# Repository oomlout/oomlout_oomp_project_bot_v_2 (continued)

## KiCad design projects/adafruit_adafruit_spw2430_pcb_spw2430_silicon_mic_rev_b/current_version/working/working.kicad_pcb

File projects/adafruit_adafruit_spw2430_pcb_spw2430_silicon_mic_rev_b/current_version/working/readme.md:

# adafruit_spw2430_pcb
 
## summary 
* id: adafruit_adafruit_spw2430_pcb_spw2430_silicon_mic_rev_b
* user: adafruit
* name: adafruit_spw2430_pcb
* board: spw2430_silicon_mic_rev_b
* repo: https://github.com/adafruit/Adafruit-SPW2430-PCB

* src_file_repo_sch: 
* src_file_repo_sch_link: https://github.com/adafruit/Adafruit-SPW2430-PCB/tree/master/
* full details link: https://github.com/oomlout/oomlout_oomp_project_bot_v_2/tree/main/projects/adafruit_adafruit_spw2430_pcb_spw2430_silicon_mic_rev_b/current_version/working  

## schematic  
  
[schematic (pdf)](working_schematic.pdf) 

## pcb  

[board (pdf)](working.pdf)  

## working_bom
| Id | Designator | Footprint | Quantity | Designation | Supplier and ref |  | None | 
| --- | --- | --- | --- | --- | --- | --- | --- | 
| 1 | C2 | 0805-NO | 1 | 0.1uF |  |  | [''] | 
| 2 | JP1 | 1X05_ROUND_76 | 1 |  |  |  | [''] | 
| 3 | U1 | SPW2430HR5H-B | 1 | SPW2430HR5H-B |  |  | [''] | 
| 4 | U2 | SOT23-5 | 1 | MIC5225-3.3 |  |  | [''] | 
| 5 | C3,C1,C4 | 0805-NO | 3 | 10uF |  |  | [''] | 
| 6 | U$12 | MOUNTINGHOLE_2.5_PLATED | 1 | MOUNTINGHOLE2.5 |  |  | [''] | 
| 7 | U$13 | PCBFEAT-REV-040 | 1 |  |  |  | [''] | 
| 8 | FID1,FID2 | FIDUCIAL_1MM | 2 | FIDUCIAL" |  |  | [''] | 
| 9 | U$5 | ADAFRUIT_3.5MM | 1 |  |  |  | [''] | 

## bom_schematic
| Ref | Qnty | Value | Cmp name | Footprint | Description | Vendor | DNP | 
| --- | --- | --- | --- | --- | --- | --- | --- | 
| C1, C3, C4 | 3 | 10uF | CAP_CERAMIC0805-NOOUTLINE | working:0805-NO |  |  |  | 
| C2 | 1 | 0.1uF | CAP_CERAMIC0805-NOOUTLINE | working:0805-NO |  |  |  | 
| FID1, FID2 | 2 | FIDUCIAL"" | FIDUCIAL{dblquote}{dblquote} | working:FIDUCIAL_1MM |  |  |  | 
| JP1 | 1 | HEADER-1X576MIL | HEADER-1X576MIL | working:1X05_ROUND_76 |  |  |  | 
| U1 | 1 | SPW2430HR5H-B | SPW2430HR5H-B | working:SPW2430HR5H-B |  |  |  | 
| U2 | 1 | MIC5225-3.3 | VREG_SOT23-5 | working:SOT23-5 |  |  |  | 
| U$12 | 1 | MOUNTINGHOLE2.5 | MOUNTINGHOLE2.5 | working:MOUNTINGHOLE_2.5_PLATED |  |  |  | 

## mounting_holes
| x | y | package | value | ref | size | 
| --- | --- | --- | --- | --- | --- | 
| 0.0 | 0.0 | MOUNTINGHOLE_2.5_PLATED | MOUNTINGHOLE2.5 | U$12 | m3 |

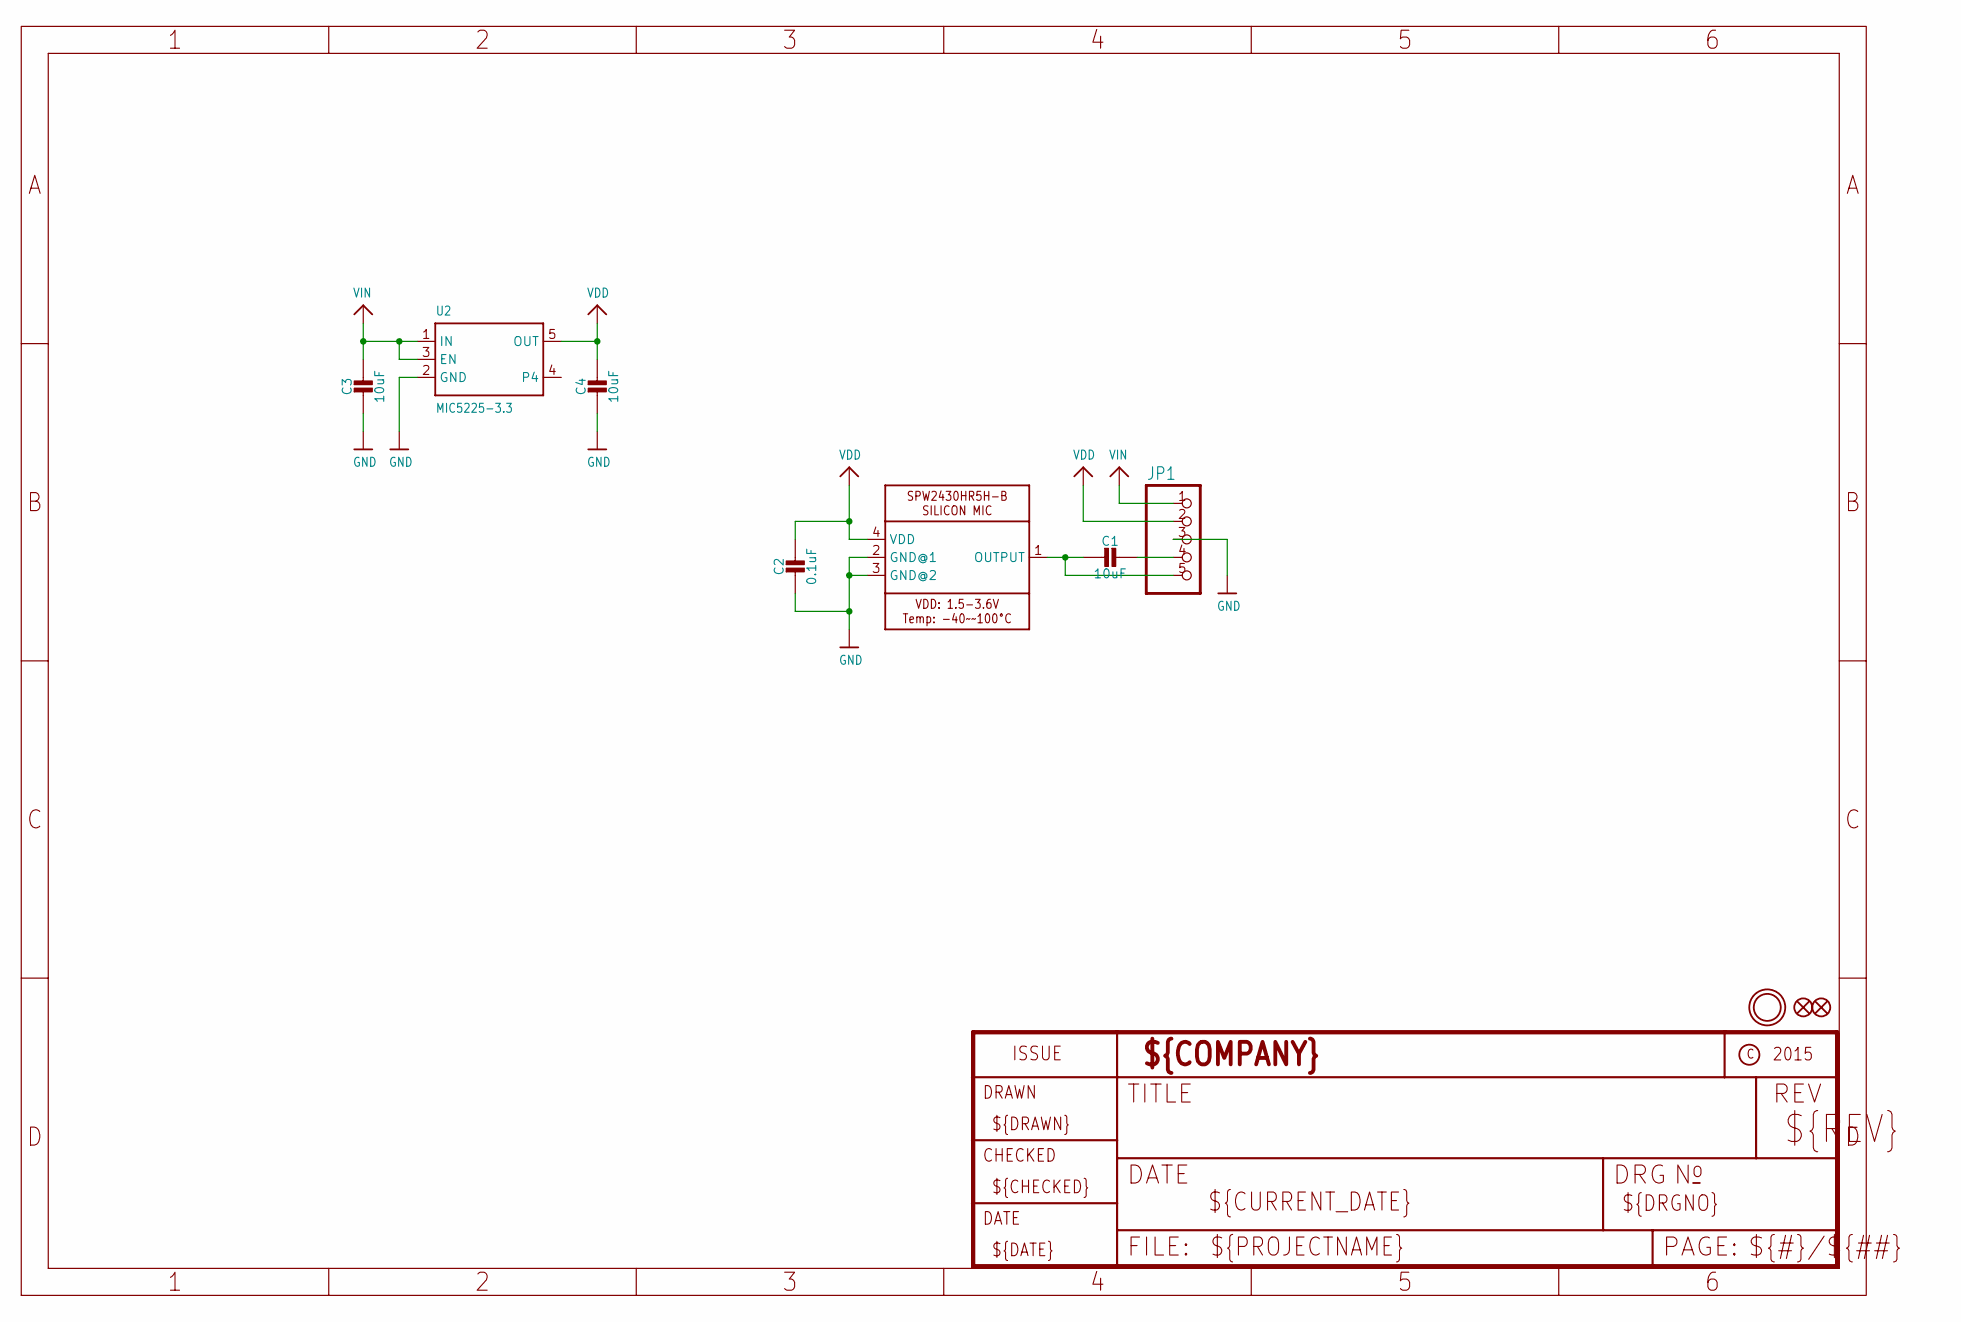
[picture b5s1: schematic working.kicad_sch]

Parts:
C1, C3, C4: 10uF; 0805-NO
C2: 0.1uF; 0805-NO
FID1, FID2: FIDUCIAL""; FIDUCIAL_1MM
JP1: HEADER-1X576MIL; 1X05_ROUND_76
U1: SPW2430HR5H-B
U2: MIC5225-3.3; SOT23-5
U$12: MOUNTINGHOLE2.5; MOUNTINGHOLE_2.5_PLATED

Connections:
GND: C2.2, C3.2, C4.2, JP1.3, U1.2 (GND@1), U1.3 (GND@2), U2.2 (GND)
unnamed: C1.2, JP1.5, U1.1 (OUTPUT)
unnamed: C1.1, JP1.4
VDD: C2.1, C4.1, JP1.2, U1.4 (VDD), U2.5 (OUT)
VIN: C3.1, JP1.1, U2.1 (IN), U2.3 (EN)

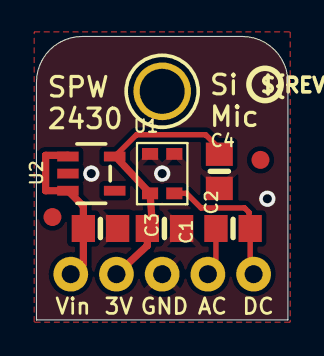
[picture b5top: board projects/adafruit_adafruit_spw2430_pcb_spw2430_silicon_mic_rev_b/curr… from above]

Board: 2 copper layers, 14.0 x 15.7 mm, 12 parts (1 on the bottom side), 5 nets.

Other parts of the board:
U$5: ADAFRUIT_3.5MM
U$13: PCBFEAT-REV-040

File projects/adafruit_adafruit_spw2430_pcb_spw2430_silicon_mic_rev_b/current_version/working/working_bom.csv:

"Id";"Designator";"Footprint";"Quantity";"Designation";"Supplier and ref";
1;"C2";"0805-NO";1;"0.1uF";;;
2;"JP1";"1X05_ROUND_76";1;"";;;
3;"U1";"SPW2430HR5H-B";1;"SPW2430HR5H-B";;;
4;"U2";"SOT23-5";1;"MIC5225-3.3";;;
5;"C3,C1,C4";"0805-NO";3;"10uF";;;
6;"U$12";"MOUNTINGHOLE_2.5_PLATED";1;"MOUNTINGHOLE2.5";;;
7;"U$13";"PCBFEAT-REV-040";1;"";;;
8;"FID1,FID2";"FIDUCIAL_1MM";2;"FIDUCIAL""";;;
9;"U$5";"ADAFRUIT_3.5MM";1;"";;;

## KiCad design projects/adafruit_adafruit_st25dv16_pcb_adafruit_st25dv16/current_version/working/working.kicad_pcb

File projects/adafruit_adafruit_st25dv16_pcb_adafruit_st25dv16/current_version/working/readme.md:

# adafruit_st25dv16_pcb
 
## summary 
* id: adafruit_adafruit_st25dv16_pcb_adafruit_st25dv16
* user: adafruit
* name: adafruit_st25dv16_pcb
* board: adafruit_st25dv16
* repo: https://github.com/adafruit/Adafruit-ST25DV16-PCB

* src_file_repo_sch: 
* src_file_repo_sch_link: https://github.com/adafruit/Adafruit-ST25DV16-PCB/tree/main/
* full details link: https://github.com/oomlout/oomlout_oomp_project_bot_v_2/tree/main/projects/adafruit_adafruit_st25dv16_pcb_adafruit_st25dv16/current_version/working  

## schematic  
  
[schematic (pdf)](working_schematic.pdf) 

## pcb  

[board (pdf)](working.pdf)  

## working_bom
| Id | Designator | Footprint | Quantity | Designation | Supplier and ref |  | None | 
| --- | --- | --- | --- | --- | --- | --- | --- | 
| 1 | @HOLE0,@HOLE1 |  | 2 |  |  |  | [''] | 
| 2 | CONN3,CONN4 | JST_SH4 | 2 | STEMMA_I2C_QT |  |  | [''] | 
| 3 | U$19,U$21 | MOUNTINGHOLE_2.5_PLATED | 2 | MOUNTINGHOLE2.5 |  |  | [''] | 
| 4 | FID3,FID4 | FIDUCIAL_1MM | 2 | FIDUCIAL_1MM |  |  | [''] | 
| 5 | D1 | CHIPLED_0603_NOOUTLINE | 1 | GREEN |  |  | [''] | 
| 6 | C1 | 0603-NO | 1 | 0.1uF |  |  | [''] | 
| 7 | R3 | RESPACK_4X0603 | 1 | 10K |  |  | [''] | 
| 8 | C3 | 0805-NO | 1 | 10uF |  |  | [''] | 
| 9 | ANT1 | NFCANT_25X15 | 1 | NFC_ANTENNA_25X15 |  |  | [''] | 
| 10 | JP1 | 1X06_ROUND_70 | 1 |  |  |  | [''] | 
| 11 | U$22 | ADAFRUIT_3.5MM | 1 |  |  |  | [''] | 
| 12 | RF1 | TSSOP8-4.4MM | 1 | ST25DVXX_TSSOP |  |  | [''] | 
| 13 | U$1 | ADAFRUIT_TEXT_20MM | 1 |  |  |  | [''] | 
| 14 | U$31,U$30 | STEMMAQT | 2 |  |  |  | [''] | 
| 15 | U$25 | PCBFEAT-REV-040 | 1 |  |  |  | [''] | 

## bom_schematic
| Ref | Qnty | Value | Cmp name | Footprint | Description | Vendor | DNP | 
| --- | --- | --- | --- | --- | --- | --- | --- | 
| ANT1 | 1 | NFC_ANTENNA_25X15 | NFC_ANTENNA_25X15 | working:NFCANT_25X15 |  |  |  | 
| C1 | 1 | 0.1uF | CAP_CERAMIC0603_NO | working:0603-NO |  |  |  | 
| C3 | 1 | 10uF | CAP_CERAMIC0805-NOOUTLINE | working:0805-NO |  |  |  | 
| CONN3, CONN4 | 2 | STEMMA_I2C_QT | STEMMA_I2C_QT | working:JST_SH4 |  |  |  | 
| D1 | 1 | GREEN | LED0603_NOOUTLINE | working:CHIPLED_0603_NOOUTLINE |  |  |  | 
| FID3, FID4 | 2 | FIDUCIAL_1MM | FIDUCIAL_1MM | working:FIDUCIAL_1MM |  |  |  | 
| JP1 | 1 | HEADER-1X670MIL | HEADER-1X670MIL | working:1X06_ROUND_70 |  |  |  | 
| R3 | 1 | 10K | RESISTOR_4PACK | working:RESPACK_4X0603 |  |  |  | 
| RF1 | 1 | ST25DVXX_TSSOP | ST25DVXX_TSSOP | working:TSSOP8-4.4MM |  |  |  | 
| U$19, U$21 | 2 | MOUNTINGHOLE2.5 | MOUNTINGHOLE2.5 | working:MOUNTINGHOLE_2.5_PLATED |  |  |  | 

## mounting_holes
| x | y | package | value | ref | size | 
| --- | --- | --- | --- | --- | --- | 
| 0.0 | 0.0 | MOUNTINGHOLE_2.5_PLATED | MOUNTINGHOLE2.5 | U$19 | m3 | 
| 20.32 | 0.0 | MOUNTINGHOLE_2.5_PLATED | MOUNTINGHOLE2.5 | U$21 | m3 |

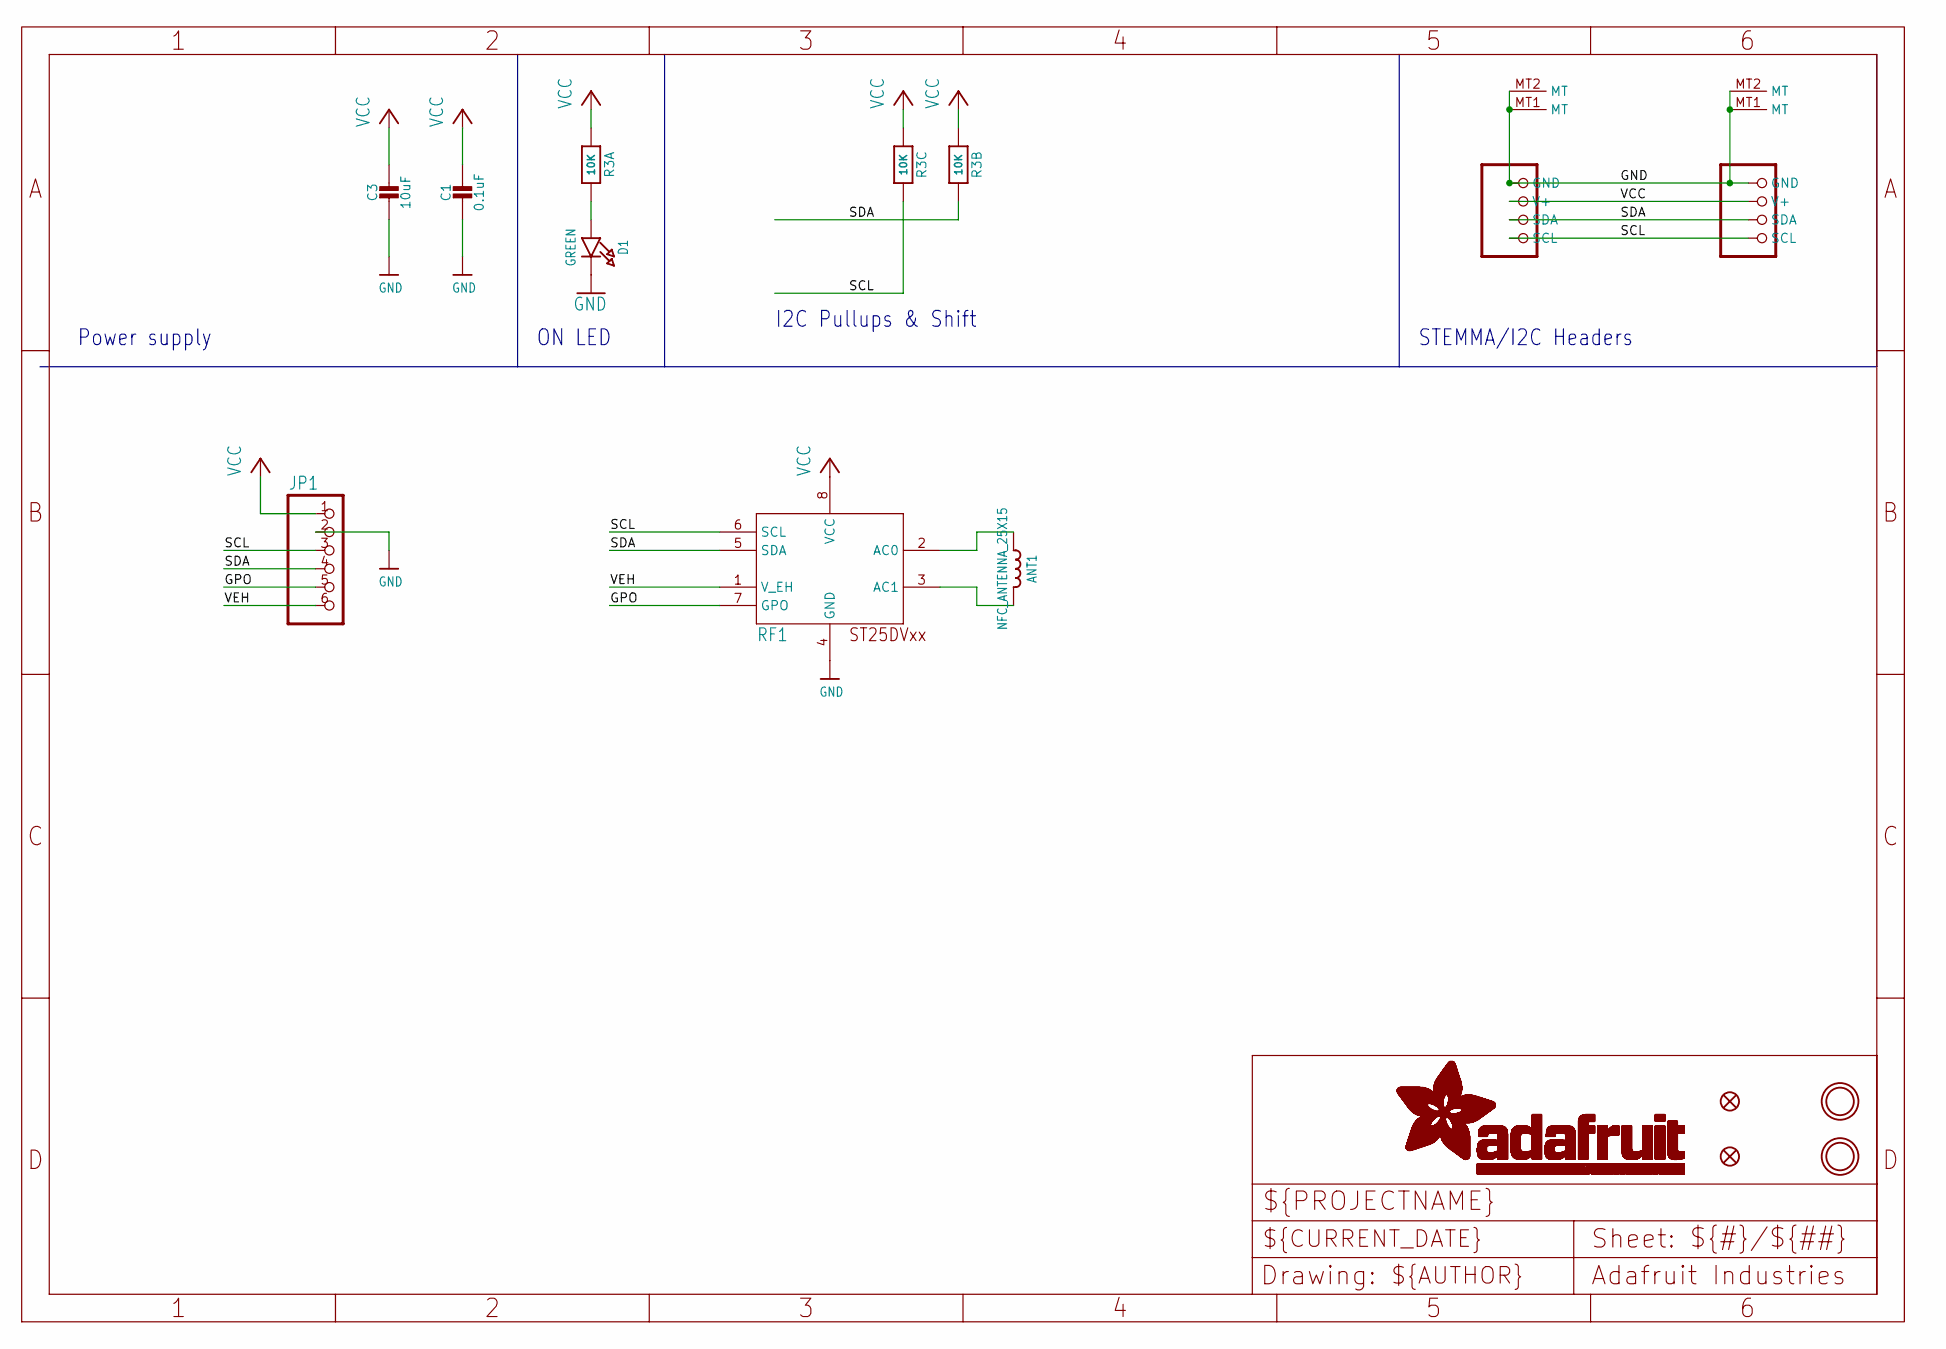
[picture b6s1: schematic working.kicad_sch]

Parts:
ANT1: NFC_ANTENNA_25X15; NFCANT_25X15
C1: 0.1uF; 0603-NO
C3: 10uF; 0805-NO
CONN3, CONN4: STEMMA_I2C_QT; JST_SH4
D1: GREEN; CHIPLED_0603_NOOUTLINE
FID3, FID4: FIDUCIAL_1MM
JP1: HEADER-1X670MIL; 1X06_ROUND_70
R3: 10K; RESPACK_4X0603
RF1: ST25DVXX_TSSOP; TSSOP8-4.4MM
U$19, U$21: MOUNTINGHOLE2.5; MOUNTINGHOLE_2.5_PLATED

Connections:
GND: C1.2, C3.2, CONN3.1 (GND), CONN3.MT1 (MT), CONN3.MT2 (MT), CONN4.1 (GND), CONN4.MT1 (MT), CONN4.MT2 (MT), D1.C, JP1.2, RF1.4 (GND)
GPO: JP1.5, RF1.7 (GPO)
unnamed: D1.A, R3.8 (2)
unnamed: ANT1.P$2 (2), RF1.2 (AC0)
unnamed: ANT1.P$1 (1), RF1.3 (AC1)
SCL: CONN3.4 (SCL), CONN4.4 (SCL), JP1.3, R3.6 (2), RF1.6 (SCL)
SDA: CONN3.3 (SDA), CONN4.3 (SDA), JP1.4, R3.7 (2), RF1.5 (SDA)
VCC: C1.1, C3.1, CONN3.2 (V+), CONN4.2 (V+), JP1.1, R3.1, R3.2 (1), R3.3 (1), RF1.8 (VCC)
VEH: JP1.6, RF1.1 (V_EH)

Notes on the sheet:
ON LED
I2C Pullups & Shift
STEMMA/I2C Headers
Power supply

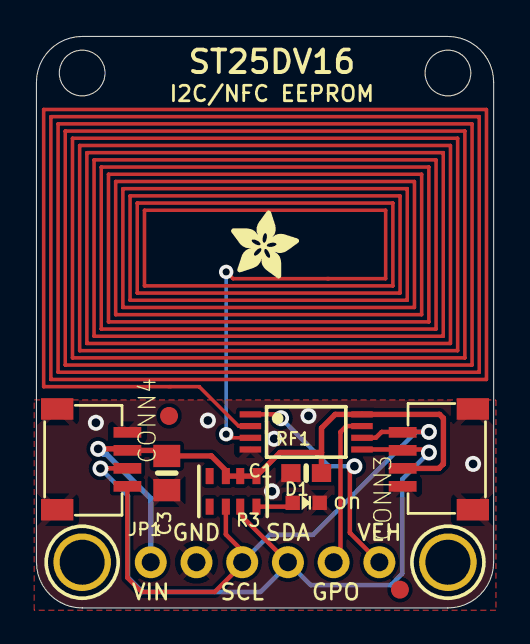
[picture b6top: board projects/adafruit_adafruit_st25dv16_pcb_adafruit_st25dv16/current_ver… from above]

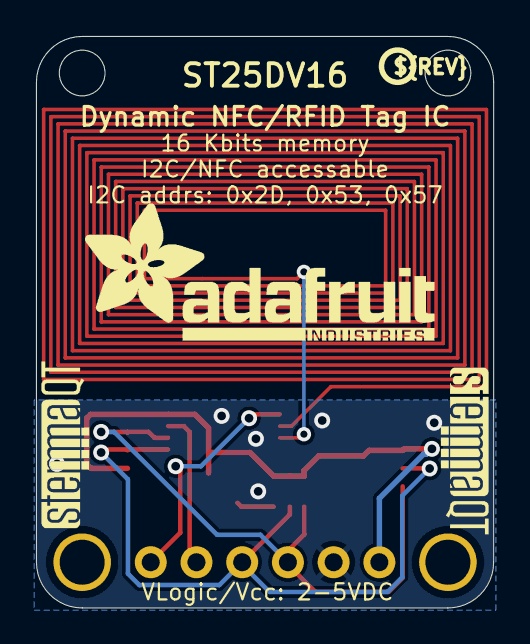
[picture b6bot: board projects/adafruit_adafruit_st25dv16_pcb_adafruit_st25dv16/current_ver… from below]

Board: 2 copper layers, 25.4 x 31.8 mm, 20 parts (4 on the bottom side), 9 nets.

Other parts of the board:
@HOLE0, @HOLE1: (no value)
U$1: ADAFRUIT_TEXT_20MM
U$22: ADAFRUIT_3.5MM
U$25: PCBFEAT-REV-040
U$30, U$31: STEMMAQT

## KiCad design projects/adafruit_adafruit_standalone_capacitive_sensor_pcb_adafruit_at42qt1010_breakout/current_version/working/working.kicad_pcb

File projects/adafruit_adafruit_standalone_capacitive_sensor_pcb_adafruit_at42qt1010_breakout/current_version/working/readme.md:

# adafruit_standalone_capacitive_sensor_pcb
 
## summary 
* id: adafruit_adafruit_standalone_capacitive_sensor_pcb_adafruit_at42qt1010_breakout
* user: adafruit
* name: adafruit_standalone_capacitive_sensor_pcb
* board: adafruit_at42qt1010_breakout
* repo: https://github.com/adafruit/Adafruit-Standalone-Capacitive-Sensor-PCB

* src_file_repo_sch: 
* src_file_repo_sch_link: https://github.com/adafruit/Adafruit-Standalone-Capacitive-Sensor-PCB/tree/master/
* full details link: https://github.com/oomlout/oomlout_oomp_project_bot_v_2/tree/main/projects/adafruit_adafruit_standalone_capacitive_sensor_pcb_adafruit_at42qt1010_breakout/current_version/working  

## schematic  
  
[schematic (pdf)](working_schematic.pdf) 

## pcb  

[board (pdf)](working.pdf)  

## working_bom
| Id | Designator | Footprint | Quantity | Designation | Supplier and ref |  | None | 
| --- | --- | --- | --- | --- | --- | --- | --- | 
| 1 | SJ1 | SOLDERJUMPER_CLOSEDWIRE | 1 | LED |  |  | [''] | 
| 2 | U$9,U$6,U$10,U$11 | MOUNTINGHOLE_2.5_PLATED | 4 | MOUNTINGHOLE2.5 |  |  | [''] | 
| 3 | SJ2 | SOLDERJUMPER_2WAY_OPEN_NOPASTE | 1 | MODE |  |  | [''] | 
| 4 | JP1 | 1X04_ROUND_76 | 1 |  |  |  | [''] | 
| 5 | LED1 | PLCC2_REVMOUNT | 1 | LS T77K-J1L2-1-0-2-R18-Z |  |  | [''] | 
| 6 | R1 | _0805 | 1 | 10K |  |  | [''] | 
| 7 | FID1,FID2 | FIDUCIAL_1MM | 2 | FIDUCIAL" |  |  | [''] | 
| 8 | C3 | _0805 | 1 | 0.1ÂµF |  |  | [''] | 
| 9 | C1 | _0805 | 1 | 22nF |  |  | [''] | 
| 10 | U1 | SOT23-6 | 1 | AT42QT1010 |  |  | [''] | 
| 11 | R2 | _0805 | 1 | 1K |  |  | [''] | 
| 12 | U$12 | ADAFRUIT_5MM | 1 |  |  |  | [''] | 
| 13 | SW1 | CAPTOUCH_SIMPLE_12.5MM | 1 | Cap pad |  |  | [''] | 

## bom_schematic
| Ref | Qnty | Value | Cmp name | Footprint | Description | Vendor | DNP | 
| --- | --- | --- | --- | --- | --- | --- | --- | 
| C1 | 1 | 22nF | CAP_CERAMIC_0805 | working:_0805 |  |  |  | 
| C3 | 1 | 0.1ÂµF | CAP_CERAMIC_0805 | working:_0805 |  |  |  | 
| FID1, FID2 | 2 | FIDUCIAL"" | FIDUCIAL{dblquote}{dblquote} | working:FIDUCIAL_1MM |  |  |  | 
| JP1 | 1 | HEADER-1X476MIL | HEADER-1X476MIL | working:1X04_ROUND_76 |  |  |  | 
| LED1 | 1 | LS T77K-J1L2-1-0-2-R18-Z | LEDPLCC2_REV | working:PLCC2_REVMOUNT |  |  |  | 
| R1 | 1 | 10K | RESISTOR_0805 | working:_0805 |  |  |  | 
| R2 | 1 | 1K | RESISTOR_0805 | working:_0805 |  |  |  | 
| SJ1 | 1 | LED | SOLDERJUMPERCLOSED | working:SOLDERJUMPER_CLOSEDWIRE |  |  |  | 
| SJ2 | 1 | MODE | SOLDERJUMPER_2WAY | working:SOLDERJUMPER_2WAY_OPEN_NOPASTE |  |  |  | 
| SW1 | 1 | Cap pad | SWITCH_CAPTOUCHATMELAT42QT | working:CAPTOUCH_SIMPLE_12.5MM |  |  |  | 
| U1 | 1 | AT42QT1010 | AT42QT1010/1 | working:SOT23-6 |  |  |  | 
| U$6, U$9, U$10, U$11 | 4 | MOUNTINGHOLE2.5 | MOUNTINGHOLE2.5 | working:MOUNTINGHOLE_2.5_PLATED |  |  |  | 

## mounting_holes
| x | y | package | value | ref | size | 
| --- | --- | --- | --- | --- | --- | 
| 15.24 | 0.0 | MOUNTINGHOLE_2.5_PLATED | MOUNTINGHOLE2.5 | U$6 | m3 | 
| 0.0 | 0.0 | MOUNTINGHOLE_2.5_PLATED | MOUNTINGHOLE2.5 | U$9 | m3 | 
| 15.24 | 22.86 | MOUNTINGHOLE_2.5_PLATED | MOUNTINGHOLE2.5 | U$10 | m3 | 
| 0.0 | 22.86 | MOUNTINGHOLE_2.5_PLATED | MOUNTINGHOLE2.5 | U$11 | m3 |

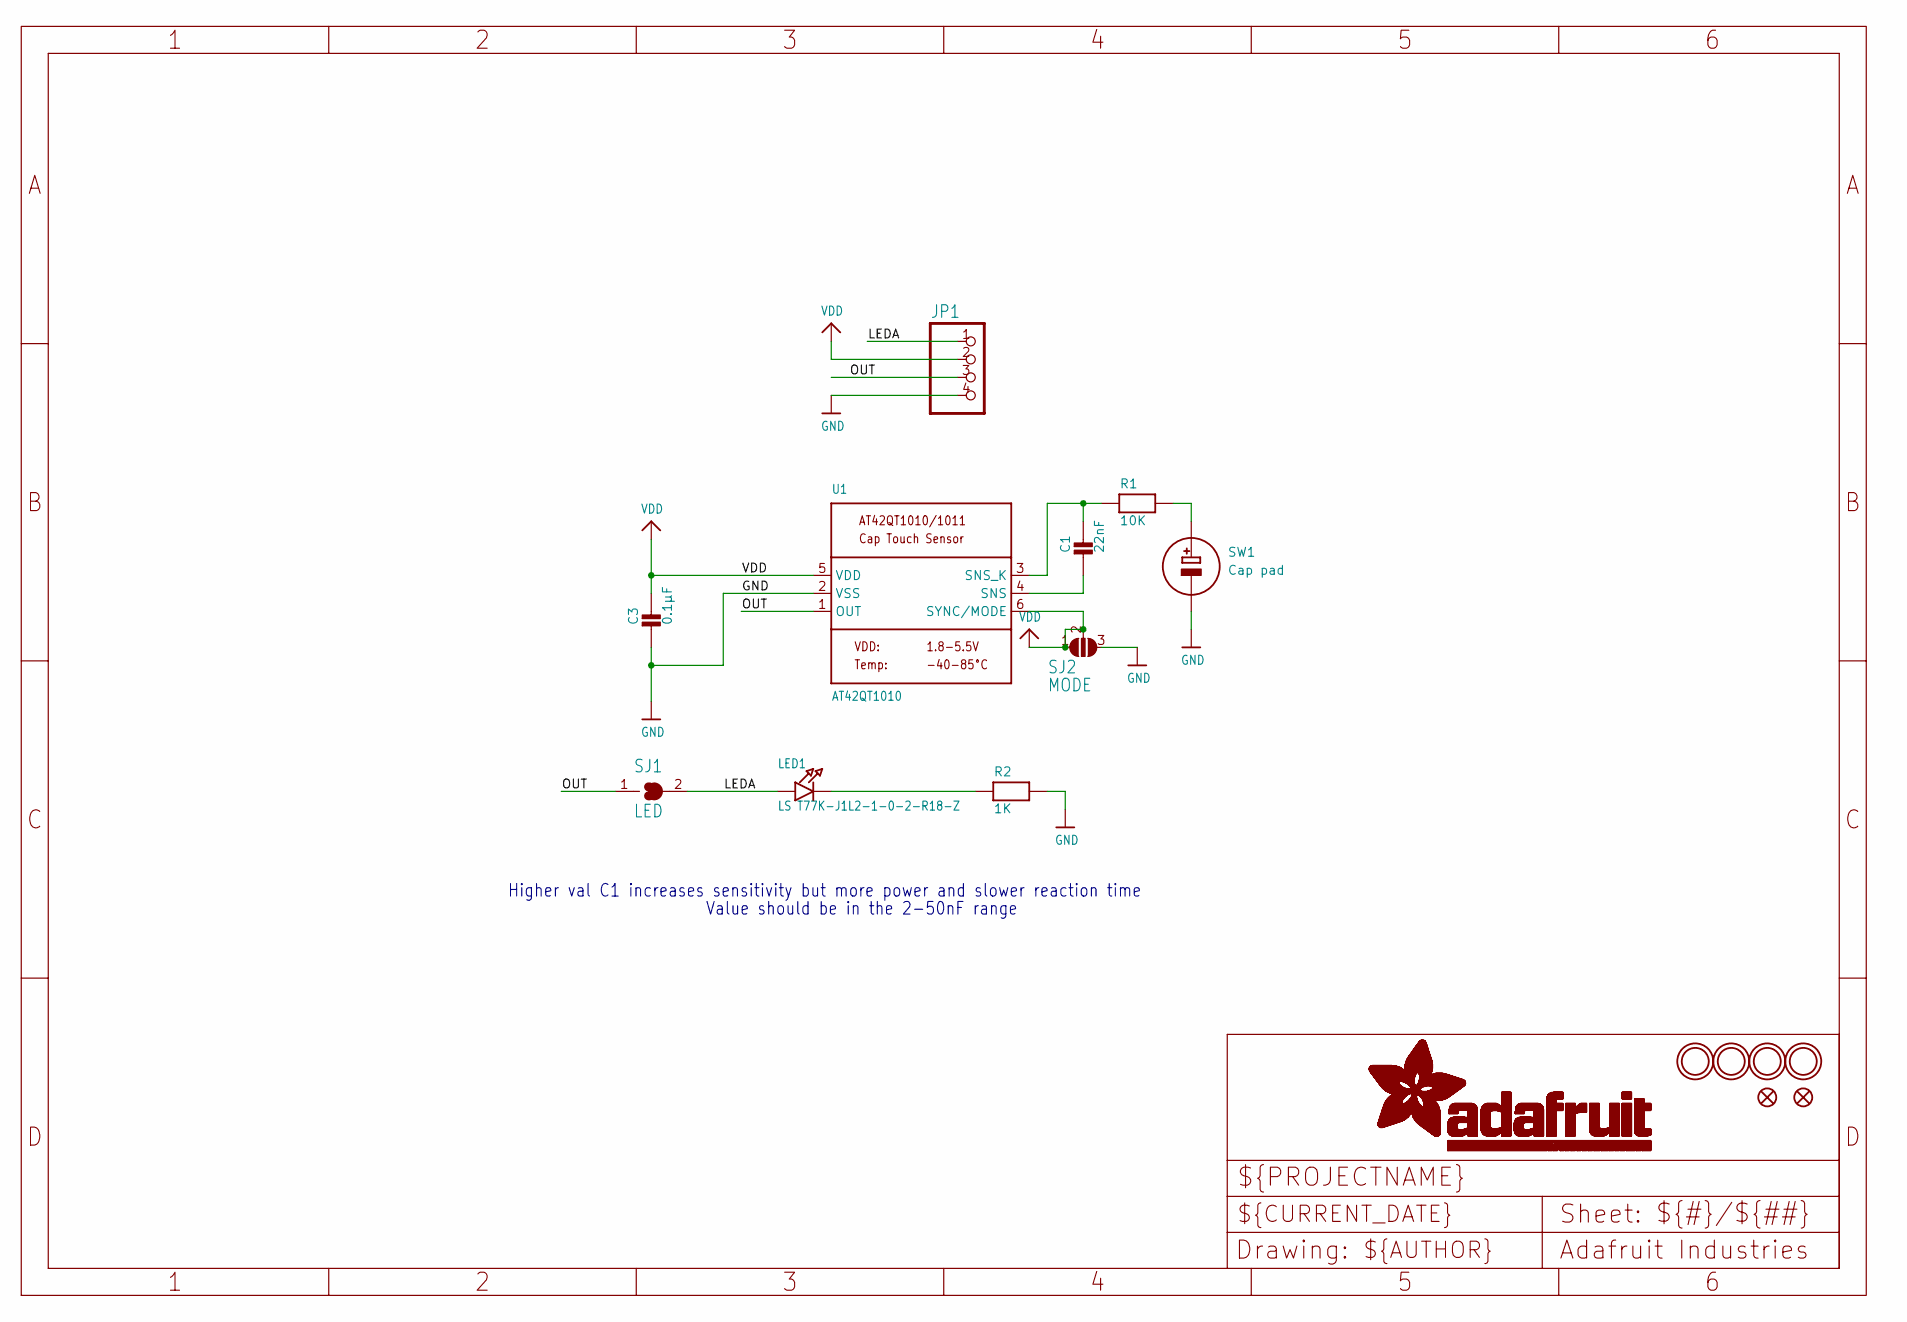
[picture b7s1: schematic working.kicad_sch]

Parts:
C1: 22nF; _0805
C3: 0.1µF; _0805
FID1, FID2: FIDUCIAL""; FIDUCIAL_1MM
JP1: HEADER-1X476MIL; 1X04_ROUND_76
LED1: LS T77K-J1L2-1-0-2-R18-Z; PLCC2_REVMOUNT
R1: 10K; _0805
R2: 1K; _0805
SJ1: LED; SOLDERJUMPER_CLOSEDWIRE
SJ2: MODE; SOLDERJUMPER_2WAY_OPEN_NOPASTE
SW1: Cap pad; CAPTOUCH_SIMPLE_12.5MM
U1: AT42QT1010; SOT23-6
U$6, U$9, U$10, U$11: MOUNTINGHOLE2.5; MOUNTINGHOLE_2.5_PLATED

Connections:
CAPPAD: R1.2, SW1.E (+)
GND: C3.2, JP1.4, R2.2, SJ2.3, SW1.G (-), U1.2 (VSS)
LEDA: JP1.1, LED1.A, SJ1.2
unnamed: C1.2, U1.4 (SNS)
unnamed: C1.1, R1.1, U1.3 (SNS_K)
unnamed: LED1.K (C), R2.1
OUT: JP1.3, SJ1.1, U1.1 (OUT)
VDD: C3.1, JP1.2, SJ2.1, SJ2.2, U1.5 (VDD), U1.6 (SYNC/MODE)

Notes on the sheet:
Value should be in the 2-50nF range
Higher val C1 increases sensitivity but more power and slower reaction time

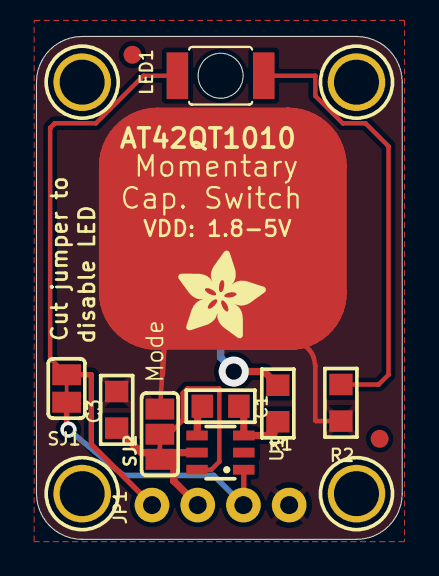
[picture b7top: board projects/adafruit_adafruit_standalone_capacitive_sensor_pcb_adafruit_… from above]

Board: 2 copper layers, 20.3 x 27.9 mm, 17 parts (1 on the bottom side), 8 nets.

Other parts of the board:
U$12: ADAFRUIT_5MM
